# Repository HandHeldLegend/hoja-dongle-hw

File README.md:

## Hoja Dongle Hardware
This is designed to be an open source dongle for Handheldlegend gamepads. 

This is essentially a Pico 2 W in a more compact form-factor, with a USB-C connector that has additional pins connected for retro game console compatibility. 
These pins use logic level translation to ensure that 5V on the pins will not damage the RP2354A Microcontroller.

Since the RM2 module is Wifi and Bluetooth capable, this could be used in many other interesting ways.

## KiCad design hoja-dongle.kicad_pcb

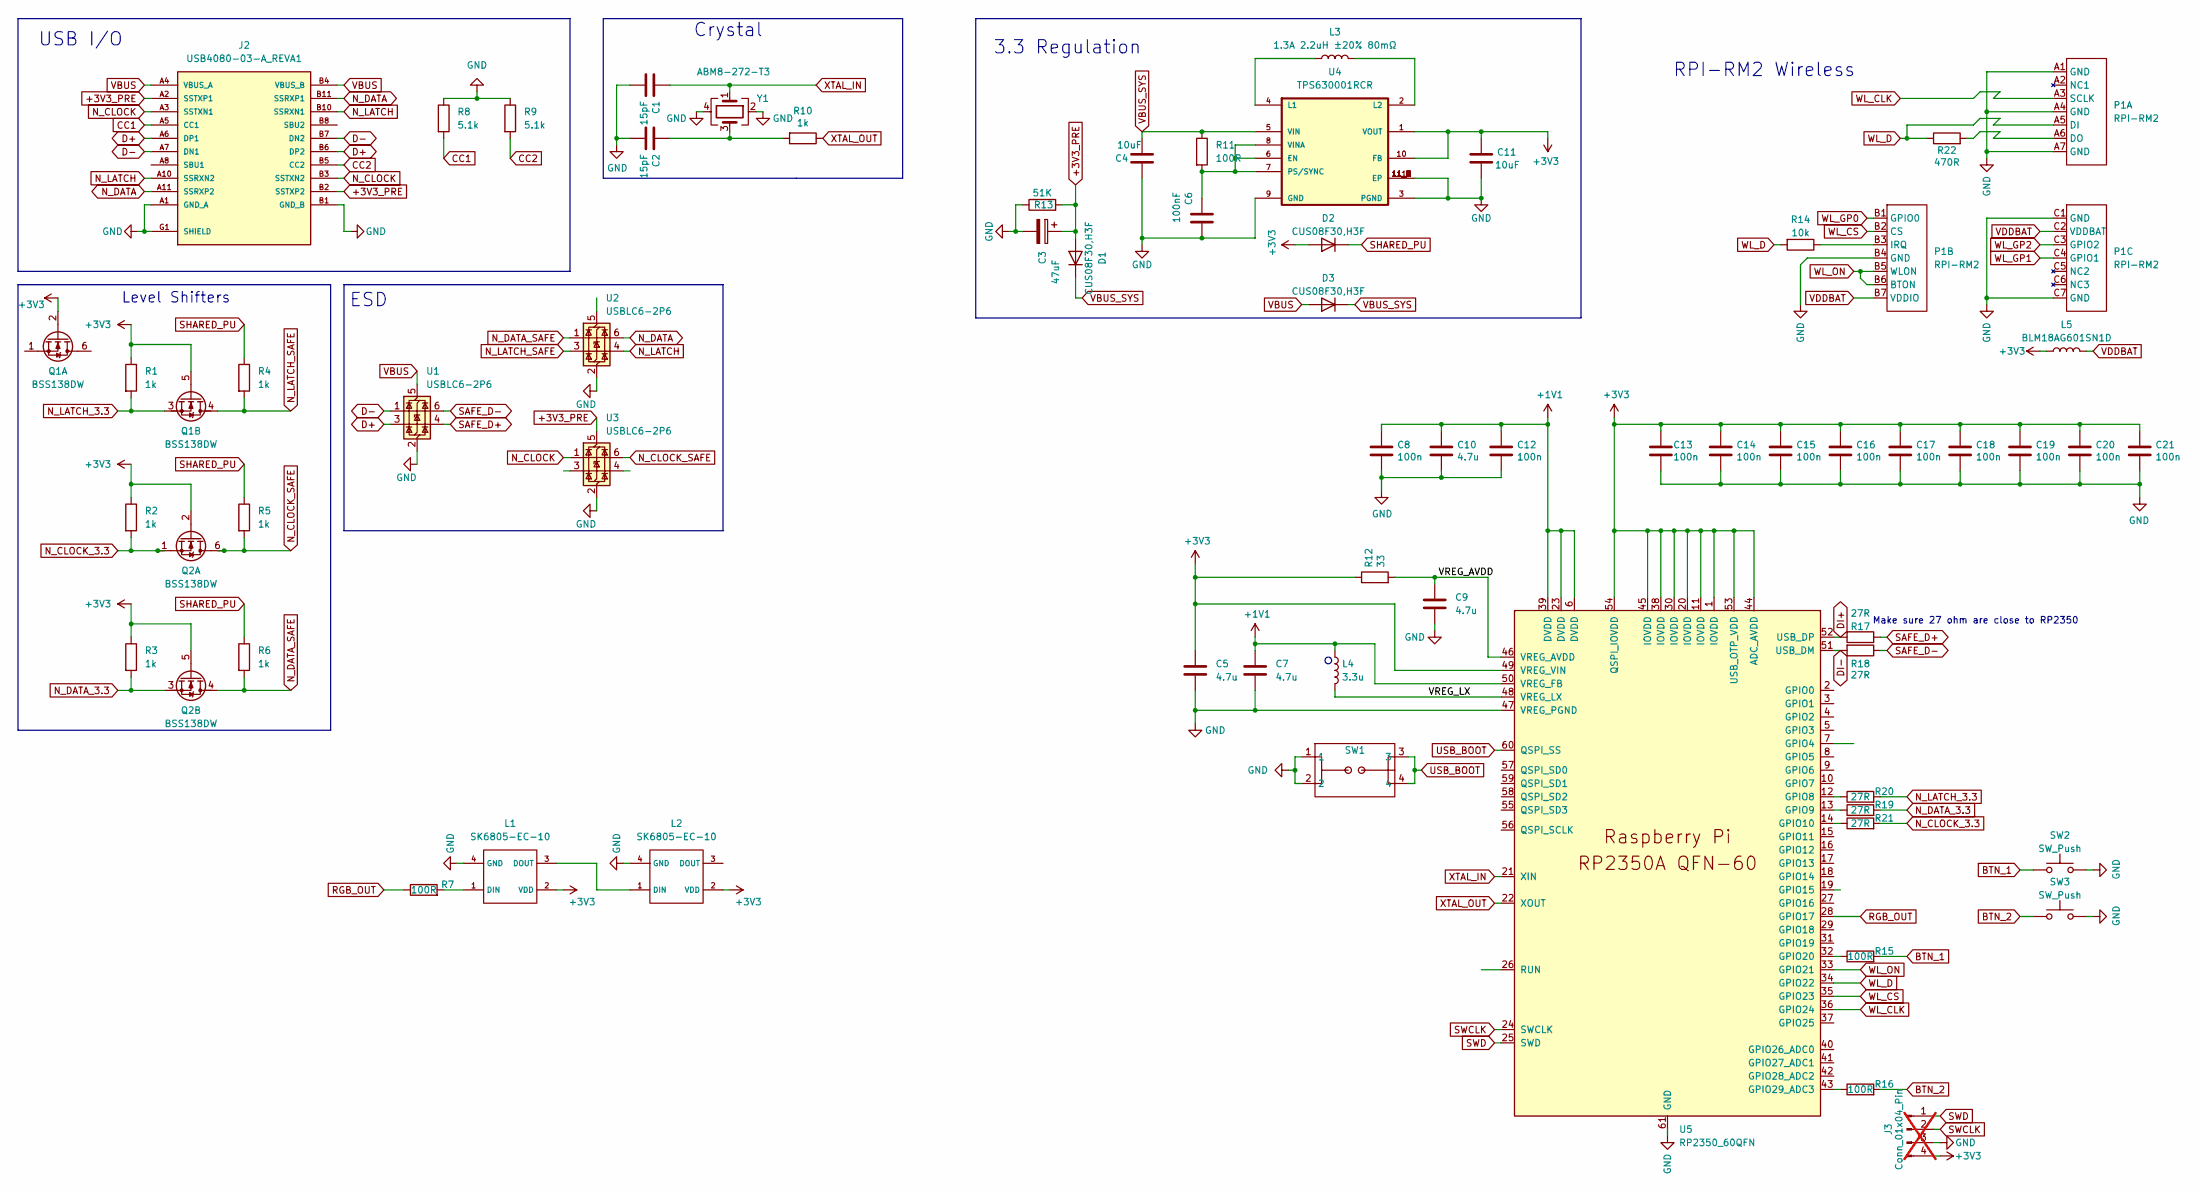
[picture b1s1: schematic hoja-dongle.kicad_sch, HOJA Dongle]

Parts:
C1, C2: 15pF; C_0402_1005Metric; MPN CC0402FRNPO9BN150; LCSC C326803
C3: 47uF; CP_EIA-3216-18_Kemet-A; MPN TAJA476K006RNJ; LCSC C7190
C4, C11: 10uF; C_0805_2012Metric; MPN CL21A106KPFNNNE; LCSC C17024
C5, C7, C9, C10: 4.7u; C_0402_1005Metric; MPN CL05A475KP5NRNC; LCSC C368809
C6: 100nF; C_0402_1005Metric; MPN CC0402KRX7R5BB104; LCSC C541406
C8, C12, C13, C14, C15, C16, C17, C18, C19, C20, C21: 100n; C_0201_0603Metric; MPN GRM033R61A104KE15D; LCSC C76934
D1, D2, D3: CUS08F30,H3F; D_SOD-323_HandSoldering; MPN CUS08F30,H3F; LCSC C150183
J2: USB4080-03-A_REVA1; GCT_USB4080-03-A_REVA1; PARTREV A1
J3: Conn_01x04_Pin; PinHeader_1x04_P2.00mm_Vertical; not fitted
L1, L2: SK6805-EC-10; MPN SK6805-EC-10
L3: 1.3A 2.2uH ±20% 80mΩ; L_1008_2520Metric; MPN MIP25202R2MBE; LCSC C315721
L4: 3.3u; L_pol_2016; MPN AOTA-B201610S3R3-101-T; LCSC C42411119
L5: BLM18AG601SN1D; L_0603_1608Metric; MPN BLM18AG601SN1D; LCSC C19330
P1: RPI-RM2; RPI_RM2; MPN RPI-RM2
Q1, Q2: BSS138DW; SOT-363_SC-70-6; MPN BSS138DW-7-F; LCSC C154900
R1, R2, R3, R4, R5, R6, R10: 1k; R_0402_1005Metric; MPN RC0402FR-071KL; LCSC C106235
R7, R11, R15, R16: 100R; R_0201_0603Metric; MPN RC0201FR-07100RL; LCSC C77623
R8, R9: 5.1k; R_0402_1005Metric; MPN RC0402FR-075K1L; LCSC C105872
R12: 33; R_0201_0603Metric; MPN RC0201FR-0733RL; LCSC C295794
R13: 51K; R_0201_0603Metric; MPN 0201WMF5102TEE0201WMF5102TEE; LCSC C473471
R14: 10k; R_0201_0603Metric; MPN RC0201FR-0710KL; LCSC C106225
R17, R18, R19, R20, R21: 27R; R_0201_0603Metric; MPN RC0201FR-0727RL; LCSC C273268
R22: 470R; R_0201_0603Metric; MPN AC0201FR-07470RL; LCSC C226558
SW1: 1TS026A-1000-0550; MPN 1TS026A-1000-0550; LCSC C913778
SW2, SW3: SW_Push; KSC-TE; MPN KSC201J LFS; LCSC C221725
U1, U2, U3: USBLC6-2P6; SOT-666; MPN USBLC6-2P6; LCSC C15999
U4: TPS630001RCR; VREG_V62_16624-01YE; MPN TPS63001DRCR; LCSC C28060
U5: RP2350_60QFN; RP2350-QFN-60-1EP_7x7_P0.4mm_EP3.4x3.4mm_ThermalVias; MPN RP2354A; LCSC C41378174
Y1: ABM8-272-T3; Crystal_SMD_3225-4Pin_3.2x2.5mm; MPN ABM8-272-T3; LCSC C20625731

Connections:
+1V1: C7.1, C8.1, C10.1, C12.1, L4.1, U5.6 (DVDD), U5.23 (DVDD), U5.39 (DVDD), U5.50 (VREG_FB)
+3V3: C5.1, C11.1, C13.1, C14.1, C15.1, C16.1, C17.1, C18.1, C19.1, C20.1, C21.1, D2.2 (A), J3.4, L1.2 (VDD), L2.2 (VDD), L5.1, Q1.2 (G1), Q1.5 (G2), Q2.2 (G1), Q2.5 (G2), R1.1, R2.1, R3.1, R12.1, U4.1 (VOUT), U4.10 (FB), U5.1 (IOVDD), U5.11 (IOVDD), U5.20 (IOVDD), U5.30 (IOVDD), U5.38 (IOVDD), U5.44 (ADC_AVDD), U5.45 (IOVDD), U5.49 (VREG_VIN), U5.53 (USB_OTP_VDD), U5.54 (QSPI_IOVDD)
+3V3_PRE: C3.1, D1.2 (A), J2.A2 (SSTXP1), J2.B2 (SSTXP2), R13.2, U3.5 (VBUS)
/VREG_AVDD: C9.1, R12.2, U5.46 (VREG_AVDD)
/VREG_LX: L4.2, U5.48 (VREG_LX)
BTN_1: R15.2, SW2.1
BTN_2: R16.2, SW3.1
CC1: J2.A5 (CC1), R8.2
CC2: J2.B5 (CC2), R9.2
D+: J2.A6 (DP1), J2.B6 (DP2), U1.3 (I/O2)
D-: J2.A7 (DN1), J2.B7 (DN2), U1.1 (I/O1)
DI+: R17.2, U5.52 (USB_DP)
DI-: R18.2, U5.51 (USB_DM)
GND: C1.2, C2.2, C3.2, C4.1, C5.2, C6.1, C7.2, C8.2, C9.2, C10.2, C11.2, C12.2, C13.2, C14.2, C15.2, C16.2, C17.2, C18.2, C19.2, C20.2, C21.2, J2.A1 (GND_A), J2.A12 (GND_A), J2.B1 (GND_B), J2.B12 (GND_B), J2.G1 (SHIELD), J2.G2 (SHIELD), J2.G3 (SHIELD), J2.G4 (SHIELD), J3.3, L1.4 (GND), L2.4 (GND), P1.A1 (GND), P1.A4 (GND), P1.A7 (GND), P1.B4 (GND), P1.C1 (GND), P1.C7 (GND), R8.1, R9.1, R13.1, SW1.1, SW1.2, SW2.2, SW3.2, U1.2 (GND), U2.2 (GND), U3.2 (GND), U4.3 (PGND), U4.9 (GND), U4.11 (EP), U4.11_1 (EP), U4.11_2 (EP), U4.11_3 (EP), U4.11_4 (EP), U4.11_5 (EP), U4.11_6 (EP), U4.11_7 (EP), U4.11_8 (EP), U5.47 (VREG_PGND), U5.61 (GND), Y1.2, Y1.4
N_CLOCK: J2.A3 (SSTXN1), J2.B3 (SSTXN2), U3.1 (I/O1)
N_CLOCK_3.3: Q2.1 (S1), R2.2, R21.2
N_CLOCK_SAFE: Q2.6 (D1), R5.2, U3.6 (I/O1)
N_DATA: J2.A11 (SSRXP2), J2.B11 (SSRXP1), U2.6 (I/O1)
N_DATA_3.3: Q2.3 (D2), R3.2, R19.2
N_DATA_SAFE: Q2.4 (S2), R6.2, U2.1 (I/O1)
N_LATCH: J2.A10 (SSRXN2), J2.B10 (SSRXN1), U2.4 (I/O2)
N_LATCH_3.3: Q1.3 (D2), R1.2, R20.2
N_LATCH_SAFE: Q1.4 (S2), R4.2, U2.3 (I/O2)
unnamed: C2.1, R10.2, Y1.3
unnamed: L1.1 (DIN), R7.2
unnamed: L1.3 (DOUT), L2.1 (DIN)
unnamed: P1.A6 (DO), R22.2
unnamed: P1.B3 (IRQ), R14.1
unnamed: C6.2, R11.2, U4.6 (EN), U4.7 (PS/SYNC), U4.8 (VINA)
unnamed: L3.1, U4.4 (L1)
unnamed: L3.2, U4.2 (L2)
unnamed: R20.1, U5.12 (GPIO8)
unnamed: R19.1, U5.13 (GPIO9)
unnamed: R21.1, U5.14 (GPIO10)
unnamed: R15.1, U5.32 (GPIO20)
unnamed: R16.1, U5.43 (GPIO29_ADC3)
RGB_OUT: R7.1, U5.28 (GPIO17)
SAFE_D+: R17.1, U1.4 (I/O2)
SAFE_D-: R18.1, U1.6 (I/O1)
SHARED_PU: D2.1 (K), R4.1, R5.1, R6.1
SWCLK: J3.2, U5.24 (SWCLK)
SWD: J3.1, U5.25 (SWD)
USB_BOOT: SW1.3, SW1.4, U5.60 (QSPI_SS)
VBUS: D3.2 (A), J2.A4 (VBUS_A), J2.A9 (VBUS_A), J2.B4 (VBUS_B), J2.B9 (VBUS_B), U1.5 (VBUS)
VBUS_SYS: C4.2, D1.1 (K), D3.1 (K), R11.1, U4.5 (VIN)
VDDBAT: L5.2, P1.B7 (VDDIO), P1.C2 (VDDBAT)
WL_CLK: P1.A3 (SCLK), U5.36 (GPIO24)
WL_CS: P1.B2 (CS), U5.35 (GPIO23)
WL_D: P1.A5 (DI), R14.2, R22.1, U5.34 (GPIO22)
WL_GP0: P1.B1 (GPIO0)
WL_GP1: P1.C4 (GPIO1)
WL_GP2: P1.C3 (GPIO2)
WL_ON: P1.B5 (WLON), P1.B6 (BTON), U5.33 (GPIO21)
XTAL_IN: C1.1, U5.21 (XIN), Y1.1
XTAL_OUT: R10.1, U5.22 (XOUT)

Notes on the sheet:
RPI-RM2 Wireless
Crystal
USB I/O
Make sure 27 ohm are close to RP2350
3.3 Regulation
Level Shifters
ESD

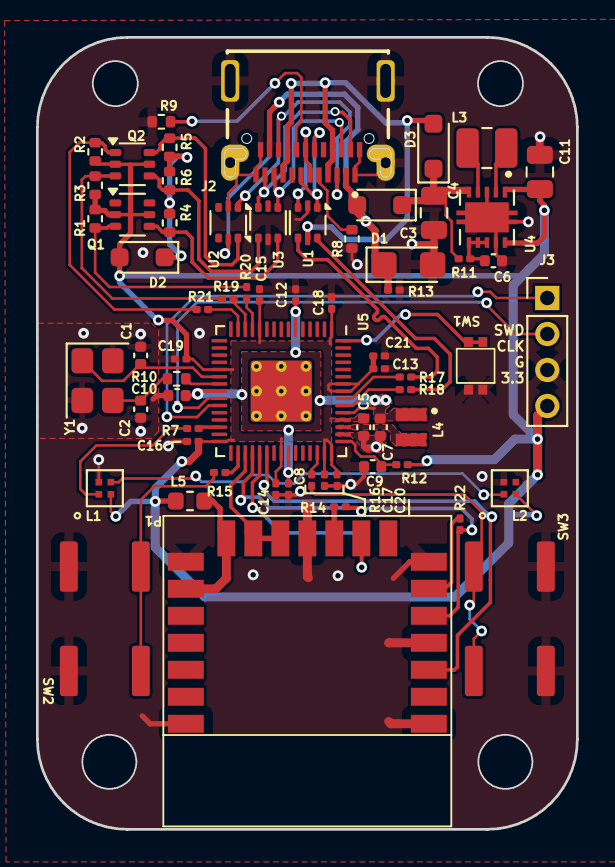
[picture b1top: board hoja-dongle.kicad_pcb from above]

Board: 2 copper layers, 30.0 x 44.0 mm, 65 parts (0 on the bottom side), 52 nets.

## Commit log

2026-01-29 Add initial README for Hoja Dongle Hardware
2026-01-29 Add image to README for better illustration
    Added an image to the README to enhance visual appeal.
2026-01-30 prod
2026-03-27 resolve missing trace
